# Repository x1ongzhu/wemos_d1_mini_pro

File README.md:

# Eagle project for Wemos D1 mini Pro

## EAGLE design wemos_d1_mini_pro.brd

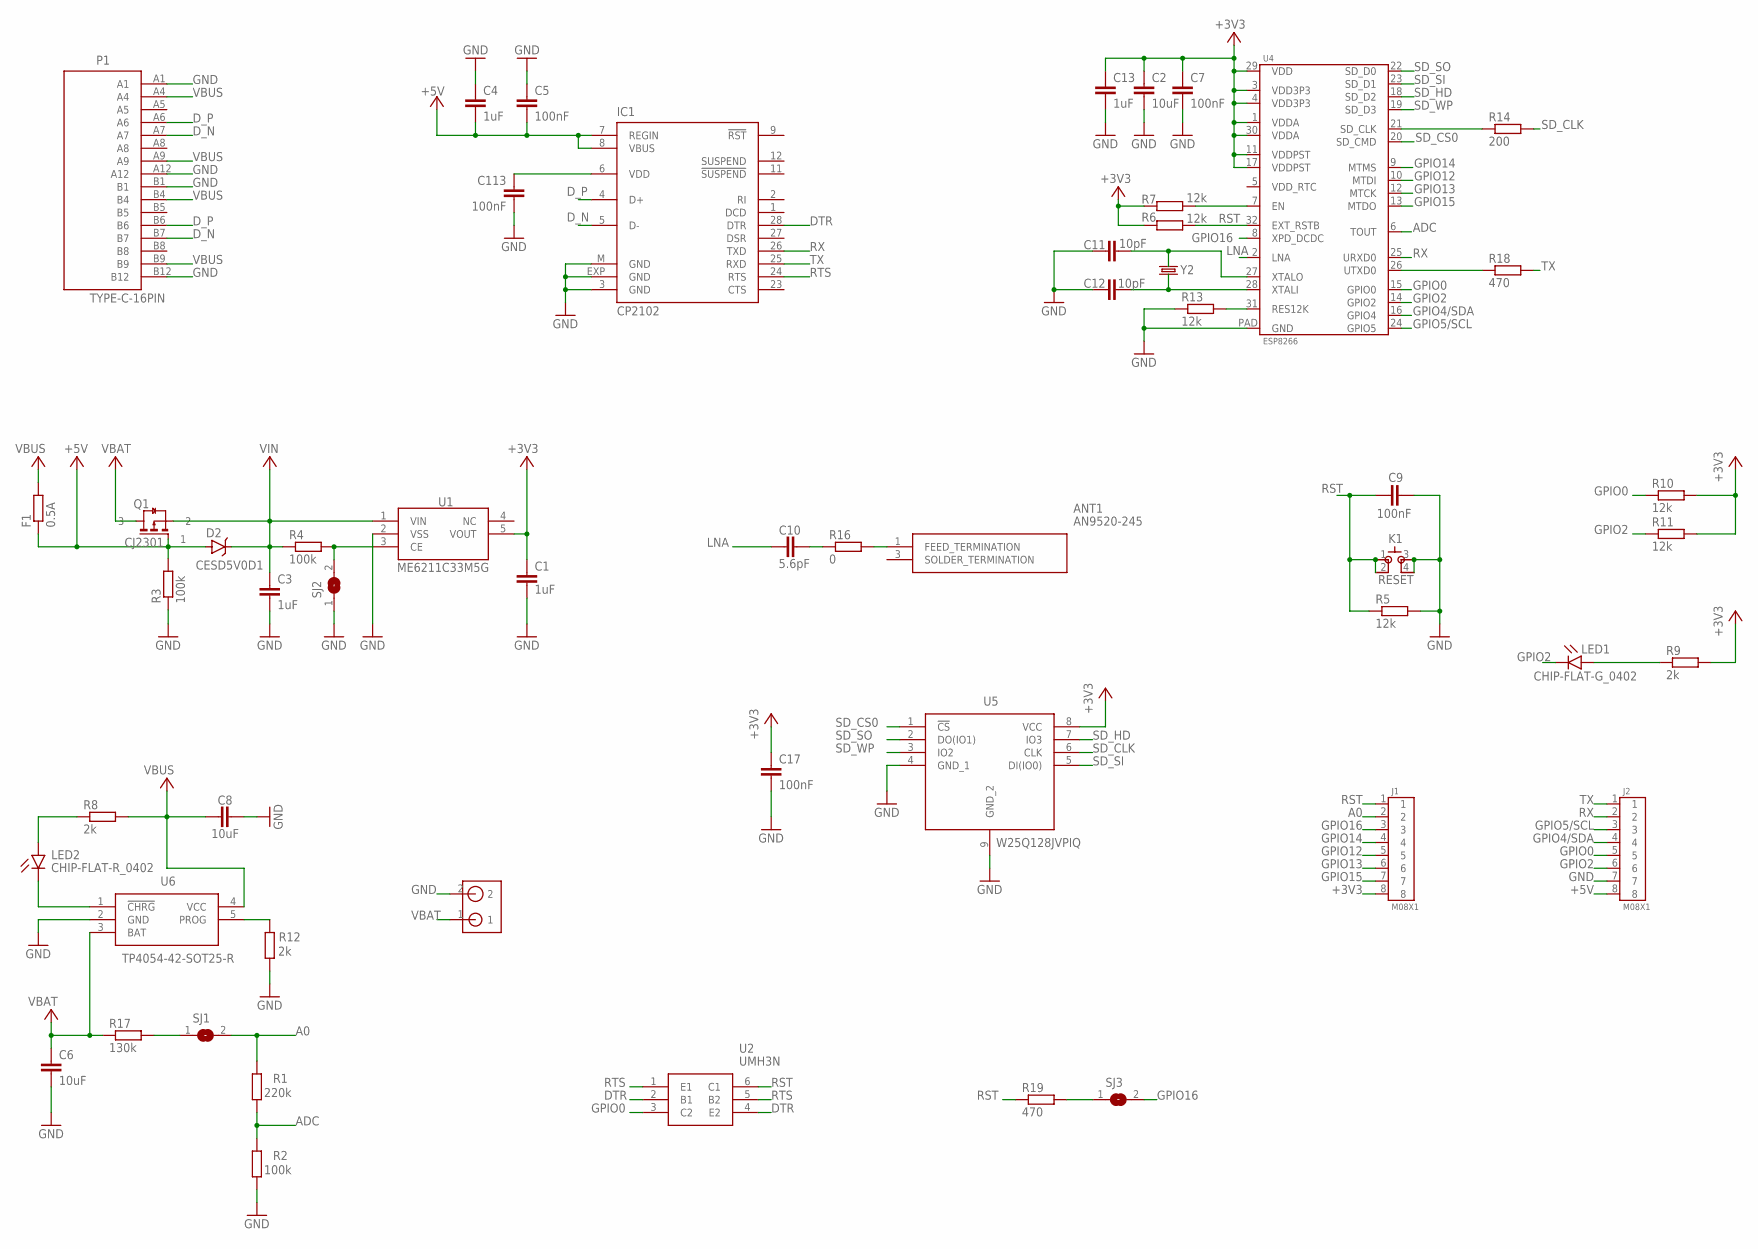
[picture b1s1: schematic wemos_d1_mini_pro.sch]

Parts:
ANT1: AN9520-245; AN9520245
C1, C3, C4, C13: 1uF; C0402
C2, C6, C8: 10uF; C0402
C5, C7, C9, C17, C113: 100nF; C0402
C10: 5.6pF; C0402
C11, C12: 10pF; C0402
D2: CESD5V0D1; SOD-123
F1: 0.5A; R0402
IC1: CP2102; MLP28
J1, J2: M08X1
K1: RESET; SKSCLDE010
LED1: CHIP-FLAT-G_0402; LEDC1005X25N_FLAT-G
LED2: CHIP-FLAT-R_0402; LEDC1005X25N_FLAT-R
P1: TYPE-C-16PIN
Q1: CJ2301; SOT95P240X115-3N
R1: 220k; R0402
R2, R3, R4: 100k; R0402
R5, R6, R7, R10, R11, R13: 12k; R0402
R8, R9, R12: 2k; R0402
R14: 200; R0402
R16: 0; R0402
R17: 130k; R0402
R18, R19: 470; R0402
SJ1, SJ2, SJ3: SJ
U1: ME6211C33M5G; SOT95P282X145-5N
U2: UMH3N; SOT65P230X110-6N
U4: ESP8266
U5: W25Q128JVPIQ; SON127P800X600X80-9N
U6: TP4054-42-SOT25-R; SOT95P280X100-5N
U$1: ZH1.25; 1.25X2-FLAT
Y2: YSX321SL; SMD-3225-4

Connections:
+3V3: C1.1, C2.1, C7.1, C13.1, C17.1, J1.8, R6.1, R7.1, R9.2, R10.2, R11.2, U1.5 (VOUT), U4.1 (VDDA), U4.3 (VDD3P3), U4.4 (VDD3P3), U4.11 (VDDPST), U4.17 (VDDPST), U4.29 (VDD), U4.30 (VDDA), U5.8 (VCC)
+5V: C4.2, C5.2, D2.A, F1.1, IC1.7 (REGIN), IC1.8 (VBUS), J2.8, Q1.1, R3.2
A0: J1.2, R1.2, SJ1.2
ADC: R1.1, R2.2, U4.6 (TOUT)
DTR: IC1.28 (DTR), U2.2 (B1), U2.4 (E2)
D_N: IC1.5 (D-), P1.A7, P1.B7
D_P: IC1.4 (D+), P1.A6, P1.B6
EN: R4.2, SJ2.2, U1.3 (CE)
GND: C1.2, C2.2, C3.2, C4.1, C5.1, C6.2, C7.2, C8.2, C9.2, C11.1, C12.1, C13.2, C17.2, C113.2, IC1.3 (GND), IC1.EXP (GND), IC1.M (GND), J2.7, K1.3 (4), K1.4 (3), P1.A1, P1.A12, P1.B1, P1.B12, R2.1, R3.1, R5.2, R12.1, R13.1, SJ2.1, U1.2 (VSS), U4.PAD (GND), U5.4 (GND_1), U5.9 (GND_2), U6.2 (GND), U$1.2
GPIO0: J2.5, R10.1, U2.3 (C2), U4.15 (GPIO0)
GPIO2: J2.6, LED1.C, R11.1, U4.14 (GPIO2)
GPIO4/SDA: J2.4, U4.16 (GPIO4)
GPIO5/SCL: J2.3, U4.24 (GPIO5)
GPIO12: J1.5, U4.10 (MTDI)
GPIO13: J1.6, U4.12 (MTCK)
GPIO14: J1.4, U4.9 (MTMS)
GPIO15: J1.7, U4.13 (MTDO)
GPIO16: J1.3, SJ3.2, U4.8 (XPD_DCDC)
LNA: C10.1, U4.2 (LNA)
unnamed: C113.1, IC1.6 (VDD)
unnamed: C12.2, U4.28 (XTALI), Y2.1
unnamed: C11.2, U4.27 (XTALO), Y2.3
unnamed: R13.2, U4.31 (RES12K)
unnamed: R7.2, U4.7 (EN)
unnamed: R12.2, U6.5 (PROG)
unnamed: C10.2, R16.1
unnamed: R14.1, U4.21 (SD_CLK)
unnamed: R18.1, U4.26 (UTXD0)
unnamed: ANT1.1 (FEED_TERMINATION), R16.2
unnamed: LED1.A, R9.1
unnamed: LED2.A, R8.1
unnamed: LED2.C, U6.1 (!CHRG)
unnamed: R17.2, SJ1.1
unnamed: R19.2, SJ3.1
RST: C9.1, J1.1, K1.1, K1.2, R5.1, R6.2, R19.1, U2.6 (C1), U4.32 (EXT_RSTB)
RTS: IC1.24 (RTS), U2.1 (E1), U2.5 (B2)
RX: IC1.26 (TXD), J2.2, U4.25 (URXD0)
SD_CLK: R14.2, U5.6 (CLK)
SD_CS0: U4.20 (SD_CMD), U5.1 (!CS)
SD_HD: U4.18 (SD_D2), U5.7 (IO3)
SD_SI: U4.23 (SD_D1), U5.5 (DI(IO0))
SD_SO: U4.22 (SD_D0), U5.2 (DO(IO1))
SD_WP: U4.19 (SD_D3), U5.3 (IO2)
TX: IC1.25 (RXD), J2.1, R18.2
VBAT: C6.1, Q1.3, R17.1, U6.3 (BAT), U$1.1
VBUS: C8.1, F1.2, P1.A4, P1.A9, P1.B4, P1.B9, R8.2, U6.4 (VCC)
VIN: C3.1, D2.C, Q1.2, R4.1, U1.1 (VIN)

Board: 2 copper layers, 54 parts (3 on the bottom side), 47 nets, no tracks yet.

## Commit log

2020-12-07 add README.md
